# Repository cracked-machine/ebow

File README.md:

# DIY Guitar Sustainer (Ebow)

[experimental THT version](Ebow_experimental_tht/README.md)

[experimental SMT version](Ebow_experimental_smt/README.md)

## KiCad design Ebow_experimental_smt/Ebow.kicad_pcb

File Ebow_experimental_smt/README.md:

- Designed to use SMT parts
- Uses [LM386](datasheets/lm386.pdf) op amp.
- Use ferrite core, wound inductors for input/output coils (`L1/L2`). See [datasheet](datasheets/2108131830_SXN-Shun-Xiang-Nuo-Elec-SMNR6028-4R7MT_C266428.pdf) for example part.
- Small magnetic should be superglued to the top of each buzzer
- Power connector `J1` should be wired to 9v battery. Observer correct polarity when wiring battery connector.
- PCB fits in Hammond 1551H enclosure. See [datasheet](datasheets/1551H.pdf) for details.

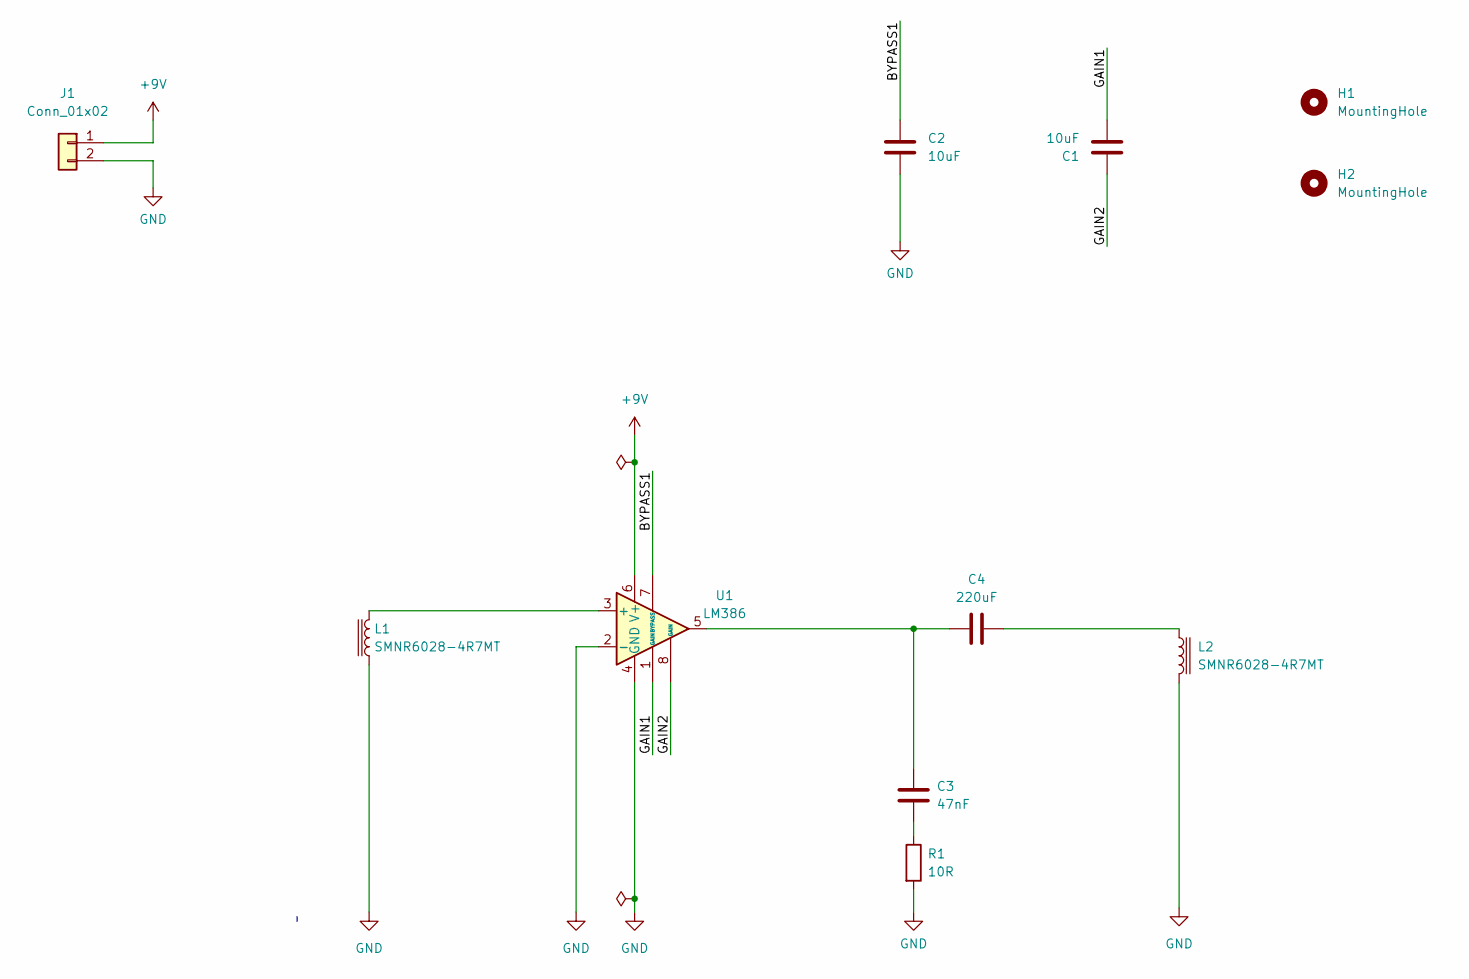
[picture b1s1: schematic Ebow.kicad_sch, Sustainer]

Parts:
C1, C2: 10uF; C_Elec_4x5.8
C3: 47nF; C_0805_2012Metric_Pad1.18x1.45mm_HandSolder
C4: 220uF; CP_Elec_8x6.9
H1, H2: MountingHole; MountingHole_2.5mm_Pad_TopBottom
J1: Conn_01x02; PinHeader_1x02_P2.54mm_Vertical
L1, L2: SMNR6028-4R7MT; L_Taiyo-Yuden_NR-80xx_HandSoldering
R1: 10R; R_0805_2012Metric_Pad1.20x1.40mm_HandSolder
U1: LM386; SOIC-8_3.9x4.9mm_P1.27mm

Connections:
+9V: J1.1, U1.6 (V+)
/BYPASS1: C2.1, U1.7 (BYPASS)
/GAIN1: C1.2, U1.1 (GAIN)
/GAIN2: C1.1, U1.8 (GAIN)
GND: C2.2, J1.2, L1.1, L2.2, R1.2, U1.2 (-), U1.4 (GND)
unnamed: C3.1, R1.1
unnamed: C3.2, C4.1, U1.5
unnamed: C4.2, L2.1
unnamed: L1.2, U1.3 (+)

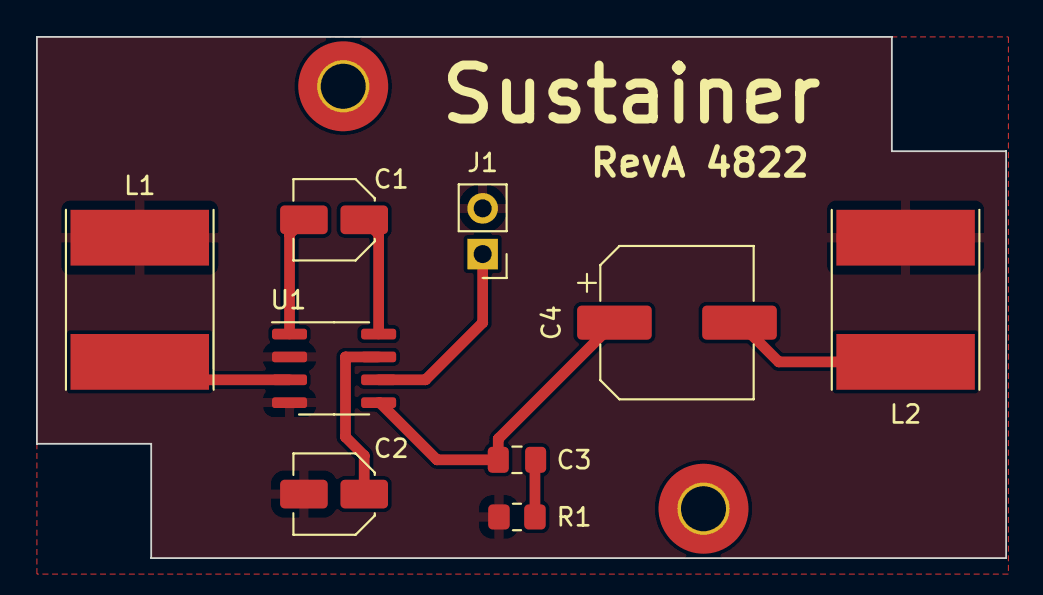
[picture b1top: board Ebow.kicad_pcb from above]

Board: 2 copper layers, 53.8 x 29.0 mm, 11 parts (0 on the bottom side), 9 nets.

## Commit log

2022-11-20 draft layout of experimental design using LM386
2022-11-20 Added readme with copper layouts
2022-11-20 spread schema design out on page and generated pdf
2022-11-20 replaced pdf schema with svg schema. Updated readme instructions
2022-12-04 Reconfigured as THT
2022-12-05 Added smt version.
2022-12-05 updated schemas
2022-12-05 updated power rail error
2022-12-05 updated svg
2022-12-05 added inductor part number (SMNR6028-4R7MT)
2022-12-05 deleted old file
